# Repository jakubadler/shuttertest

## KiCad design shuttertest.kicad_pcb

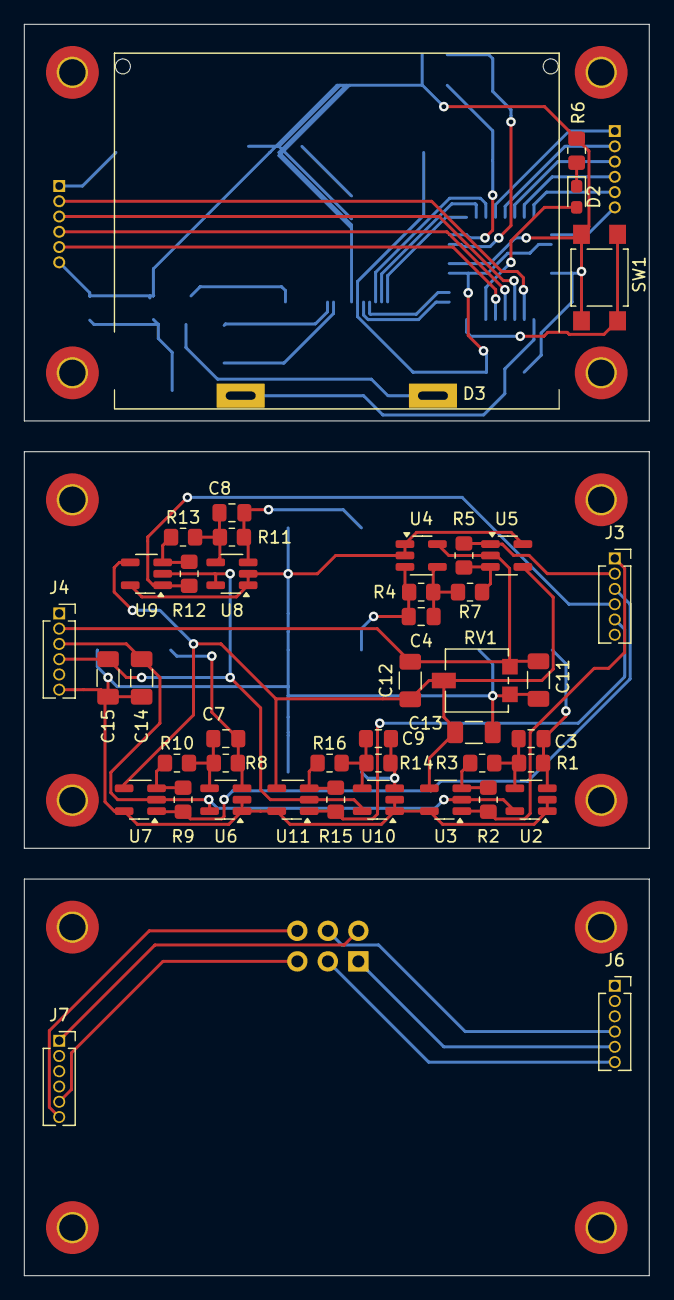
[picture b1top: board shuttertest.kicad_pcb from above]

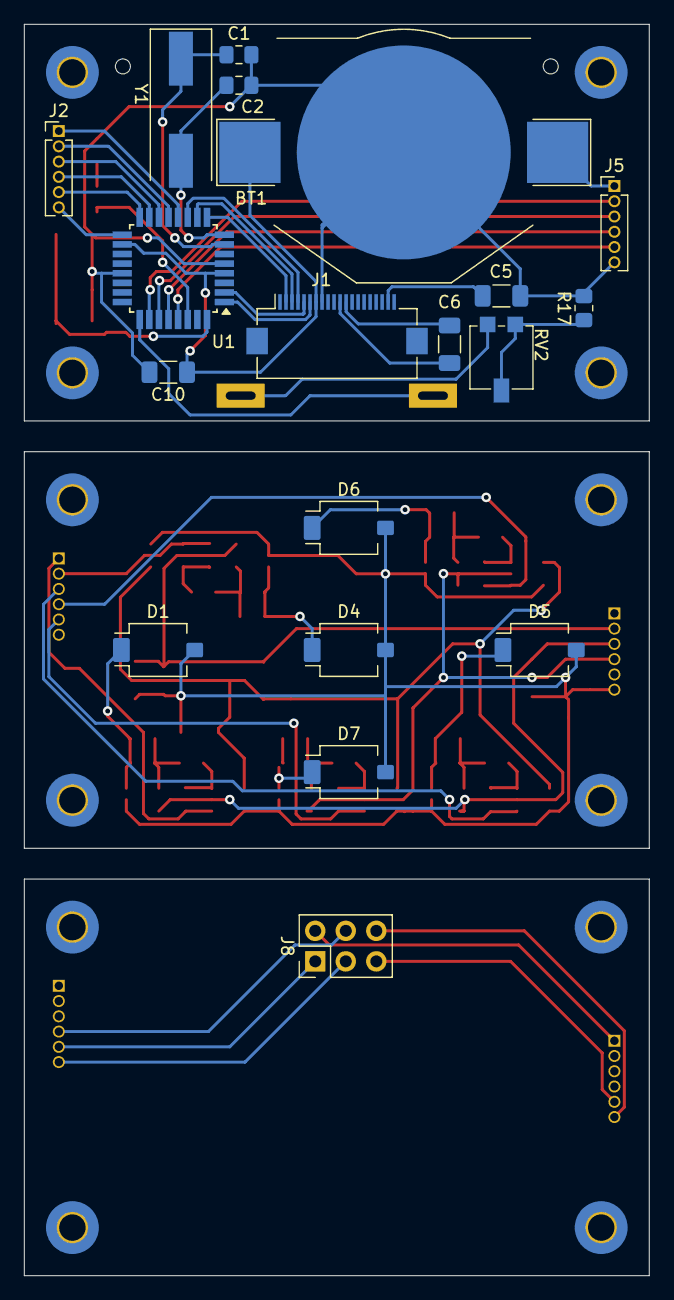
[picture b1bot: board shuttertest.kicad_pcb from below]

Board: 2 copper layers, 52.0 x 104.1 mm, 63 parts (19 on the bottom side), 54 nets.

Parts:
BT1: Battery_Cell; BatteryHolder_Keystone_3002_1x2032
C1, C2: 22p; C_0805_2012Metric_Pad1.18x1.45mm_HandSolder
C3, C4, C7, C8, C9: C; C_0805_2012Metric_Pad1.18x1.45mm_HandSolder
C5, C6, C10, C11, C12, C13, C14, C15: 100n; C_1206_3216Metric_Pad1.33x1.80mm_HandSolder
D1, D4, D5, D6, D7: BPW34-SMD; Osram_BPW34S-SMD
D2: LED; LED_0603_1608Metric_Pad1.05x0.95mm_HandSolder
D3: LED; DEM_128064N
J1: Conn_01x20_Female; Hirose_FH12-20S-0.5SH_1x20-1MP_P0.50mm_Horizontal
J2, J5: Conn_01x06_Male; PinHeader_1x06_P1.27mm_Vertical
J3, J4, J6, J7: Conn_01x06_Female; PinSocket_1x06_P1.27mm_Vertical
J8: AVR-ISP-6; PinHeader_2x03_P2.54mm_Vertical
R1, R4, R8, R11, R14: 2M2; R_0805_2012Metric_Pad1.20x1.40mm_HandSolder
R2, R5, R9, R12, R15: 6k8; R_0805_2012Metric_Pad1.20x1.40mm_HandSolder
R3, R7, R10, R13, R16: 2k7; R_0805_2012Metric_Pad1.20x1.40mm_HandSolder
R6: R; R_0805_2012Metric_Pad1.20x1.40mm_HandSolder
R17: 68; R_0805_2012Metric_Pad1.20x1.40mm_HandSolder
RV1: 100k; Potentiometer_Vishay_TS53YL_Vertical
RV2: 220; Potentiometer_Vishay_TS53YL_Vertical
SW1: SW_Push; SW_SPST_TL3305A
U1: ATmega328PB-A; TQFP-32_7x7mm_P0.8mm
U2, U4, U6, U8, U10: LM321; SOT-23-5_HandSoldering
U3, U5, U7, U9, U11: MCP6561R; SOT-23-5_HandSoldering
Y1: 8M; Crystal_SMD_HC49-SD

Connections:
+3V0: BT1.1 (+), C10.1, J1.7, J5.1, U1.4 (VCC), U1.18 (AVCC)
GND: BT1.2 (-), C1.1, C2.1, C5.2, C10.2, J1.8, J5.6, R6.2, R17.2, SW1.1, U1.5 (GND), U1.21 (GND)
GND1: C11.2, C13.2, C14.2, C15.2, D1.2 (A), D4.2 (A), D5.2 (A), D6.2 (A), D7.2 (A), J4.6, RV1.3, U2.1 (+), U2.2 (V-), U3.5 (V-), U4.1 (+), U4.2 (V-), U5.5 (V-), U6.1 (+), U6.2 (V-), U7.5 (V-), U8.1 (+), U8.2 (V-), U9.5 (V-), U10.1 (+), U10.2 (V-), U11.5 (V-)
GND2: J7.6, J8.6 (GND)
unnamed: C3.2, R1.1, R3.2, U2.4
unnamed: C4.2, R4.1, R7.2, U4.4
unnamed: C7.2, R8.1, R10.2, U6.4
unnamed: C8.2, R11.1, R13.2, U8.4
unnamed: C9.2, R14.1, R16.2, U10.4
unnamed: C3.1, D1.1 (K), R1.2, U2.3 (-)
unnamed: D2.2 (A), U1.30 (PD0)
unnamed: D2.1 (K), R6.1
unnamed: D3.1 (K), RV2.1
unnamed: C4.1, D4.1 (K), R4.2, U4.3 (-)
unnamed: C7.1, D5.1 (K), R8.2, U6.3 (-)
unnamed: C8.1, D6.1 (K), R11.2, U8.3 (-)
unnamed: C9.1, D7.1 (K), R14.2, U10.3 (-)
unnamed: J1.2, U1.9 (PD5)
unnamed: J1.3, U1.10 (PD6)
unnamed: J1.4, U1.11 (PD7)
unnamed: J1.5, U1.2 (PD4)
unnamed: J1.6, U1.1 (PD3)
unnamed: C6.2, J1.11
unnamed: C6.1, J1.12
unnamed: C5.1, J1.19
unnamed: J2.1, U1.12 (PB0)
unnamed: J2.2, U1.13 (PB1)
unnamed: J2.3, U1.14 (PB2)
unnamed: J2.4, U1.15 (PB3)
unnamed: J2.5, U1.16 (PB4)
unnamed: J2.6, U1.17 (PB5)
unnamed: J3.1, R2.2, U3.1
unnamed: J3.2, R5.2, U5.1
unnamed: J3.3, R9.2, U7.1
unnamed: J3.4, R12.2, U9.1
unnamed: J3.5, R15.2, U11.1
unnamed: J5.2, U1.26 (PC3)
unnamed: J5.3, U1.27 (PC4)
unnamed: J5.4, U1.28 (PC5)
unnamed: J5.5, U1.29 (~RESET/PC6)
unnamed: J6.4, J8.4 (MOSI)
unnamed: J6.5, J8.1 (MISO)
unnamed: R17.1, RV2.2, RV2.3
unnamed: SW1.2, U1.32 (PD2)
unnamed: C1.2, U1.7 (XTAL1/PB6), Y1.1
unnamed: C2.2, U1.8 (XTAL2/PB7), Y1.2
unnamed: R2.1, R3.1, U3.3 (+)
unnamed: R5.1, R7.1, U5.3 (+)
unnamed: R9.1, R10.1, U7.3 (+)
unnamed: R12.1, R13.1, U9.3 (+)
unnamed: R15.1, R16.1, U11.3 (+)
unnamed: C12.2, C13.1, RV1.2, U3.4 (-), U5.4 (-), U7.4 (-), U9.4 (-), U11.4 (-)
VCC: C11.1, C12.1, J4.2, RV1.1, U4.5 (V+), U5.2 (V+)
VDD: J7.1, J8.2 (VCC)

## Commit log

2024-10-12 Initial design
2024-10-12 Use through-hole connectors on bottom board
2024-11-11 Unify panel gap
2024-11-27 2.54mm pitch AVR ISP header
2026-01-29 Bump to KiCad 9
2026-01-30 Add fixed series resistor to backight trimpot
